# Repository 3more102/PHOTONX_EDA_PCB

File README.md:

# PHOTONX EDA PCB

**Evidence-driven PCB manufacturing-data reconstruction and reverse engineering.**

PHOTONX converts PCB manufacturing evidence into an auditable engineering model: geometry, drills and slots, physical connectivity, reconstructed nets, component and semantic hypotheses, validation evidence, review artifacts, and experimental KiCad output.

> **Core rule: unknown stays unknown.**  
> PHOTONX records provenance, confidence, assumptions, conflicts, omissions, and unresolved state instead of silently turning missing design intent into plausible-looking facts.

**Jump to:** [Quick start](#quick-start) · [Use cases](#where-photonx-fits) · [Flow charts](#reconstruction-flow-chart) · [Pipeline](#reconstruction-pipeline) · [Architecture](#architecture-layers) · [Evidence model](#evidence-model) · [Capabilities](#capability-matrix) · [Python API](#python-api) · [Review checklist](#how-to-review-a-reconstruction) · [Verification](#verification-and-ci) · [Roadmap](#roadmap) · [Documentation](#documentation)

### Visual maps

| Map | Purpose |
|---|---|
| [Reconstruction flow](#reconstruction-flow-chart) | End-to-end manufacturing-data reconstruction |
| [Architecture map](#architecture-layers) | Software and evidence-layer organization |
| [Evidence escalation](#evidence-model) | Observed → derived → inferred → corroborated claims |
| [Human review flow](#how-to-review-a-reconstruction) | Decision path for ambiguous findings |
| [Validation / release flow](#validation-stack) | Tests, round-trip checks, and readiness gates |
| [Parser decision flow](#parsing-and-manufacturing-geometry) | Strict vs permissive handling of unsupported syntax |
| [KiCad export flow](#kicad-export-policy) | Conservative export and native-validation decision path |
| [CLI execution flow](#quick-start) | Command dispatch, bundle generation, optional KiCad export, and exit codes |

---

## Why PHOTONX

PCB manufacturing data preserves **physical implementation** much more reliably than it preserves **original design intent**. A Gerber or drill package can prove that copper, holes, pads, and mechanical features existed; it usually cannot prove the original schematic hierarchy, semantic net names, component values, firmware behavior, or engineering rationale.

PHOTONX is built around that distinction.

| Principle | PHOTONX behavior |
|---|---|
| **Evidence before inference** | Source facts and deterministic derivations are kept separate from hypotheses. |
| **Strict parsing** | Unsupported syntax is rejected or diagnosed rather than silently approximated. |
| **Deterministic reconstruction** | Stable ordering and deterministic IDs make repeated runs auditable and diffable. |
| **Conservative semantics** | Physical copper groups are not automatically promoted to original logical nets. |
| **Explicit uncertainty** | Unknown plating, identity, layer span, values, and intent remain unknown until evidence supports them. |
| **Reproducible validation** | Reconstruction, validation, regression evidence, round-trip checks, and release-readiness logic are kept testable. |

### Current verified snapshot

| Item | Verified state |
|---|---|
| Package | **0.2.0** |
| Python | **3.11+** |
| Main dependencies | **NetworkX**, **Shapely** |
| Verified change set | **PR #54 head `c1fd9fc`, merged as `8ba238d` — 19 Sep 2026** |
| CI matrix | Python **3.11**, **3.12**, **3.13** |
| Test result | **855 passed, 2 warnings** on each CI matrix job |
| CI run | [GitHub Actions run 35431302455](https://github.com/3more102/PHOTONX_EDA_PCB/actions/runs/35431302455) |

PHOTONX is an active engineering platform. It is **not** a complete CAM replacement, electrical sign-off tool, safety certification system, or fabrication guarantee.

---

## Where PHOTONX fits

PHOTONX is most useful when the available evidence is **manufacturing-centric** and the goal is to recover an auditable engineering model without overstating certainty.

| Workflow | What PHOTONX contributes | Boundary |
|---|---|---|
| **Legacy PCB analysis** | Reconstructs geometry, physical connectivity, board features, and evidence-backed hypotheses | Does not recreate unavailable original intent by assumption |
| **Repair / obsolescence investigation** | Helps expose physical nets, component neighborhoods, interfaces, power evidence, and candidate functions | Exact identity still requires markings, BOM, measurements, or other evidence |
| **Design recovery / migration** | Produces structured board data, review artifacts, and experimental KiCad representations | Generated CAD must be reviewed before production use |
| **Manufacturing-data QA** | Surfaces parser diagnostics, geometry issues, validation findings, omissions, and source provenance | Not a fabrication-house sign-off |
| **Research and benchmarking** | Supports deterministic replay, regression fixtures, ground-truth governance, and explicit confidence | Synthetic fixtures remain synthetic evidence |
| **EDA experimentation** | Provides modular parsers, geometry/connectivity APIs, inference layers, exports, and review infrastructure | Production support is limited to declared syntax and semantics |

### PHOTONX is deliberately not

- an automatic “Gerber to perfect schematic” converter;
- a substitute for original source CAD when that source still exists;
- a guarantee that a guessed component, net role, or functional block is correct;
- an SI/PI, EMC, safety, regulatory, or fabrication-certification authority;
- a reason to discard uncertainty that the source package cannot resolve.

---

## Quick start

### Install

```bash
python -m pip install -e ".[test]"
```

### Optional C++17 spatial acceleration

PHOTONX can accelerate spatial broad-phase candidate generation with an optional C++17 shared library while keeping exact Python/Shapely and Euclidean predicates authoritative for connectivity, DRC, and radius acceptance.

```bash
cmake -S native -B build/native -DCMAKE_BUILD_TYPE=Release
cmake --build build/native --config Release
export PHOTONX_NATIVE_LIBRARY="$PWD/build/native/lib/libphotonx_native.so"
pytest -q
```

For a self-contained platform wheel, install the `build` frontend and opt in during wheel creation:

```bash
python -m pip install build
PHOTONX_BUILD_NATIVE=1 python -m build --wheel
```

A normal wheel/install remains Python-only and does not require a compiler. Native-enabled wheels embed the shared library inside the package, so `backend="auto"` can discover it without `PHOTONX_NATIVE_LIBRARY`. See [Native acceleration](docs/NATIVE_ACCELERATION.md) for Windows syntax, the ABI check, safety contract, and staged roadmap.

### Inspect declared parser capabilities

```bash
photonx capabilities
```

### Reconstruct a manufacturing-data directory

```bash
photonx reconstruct examples/PHOTONX_LED_TEST/input --output build/led
```

### Request experimental KiCad PCB output

```bash
photonx reconstruct examples/PHOTONX_LED_TEST/input \
  --output build/led \
  --kicad
```

### Emit review artifacts

```bash
photonx reconstruct examples/PHOTONX_LED_TEST/input \
  --output build/led \
  --review-artifacts
```

This emits a cohesive `review/` bundle with Markdown, JSON, JUnit, SVG, GraphML, and CSV artifacts.

### Request individual review exports

```bash
photonx reconstruct examples/PHOTONX_LED_TEST/input \
  --output build/led \
  --svg --graphml --csv
```

These flags emit `reconstructed.svg`, `reconstructed.graphml`, and CSV net/component tables independently.

### Use permissive parsing intentionally

Strict behavior is preferred. Permissive mode exists for workflows where unsupported constructs should be preserved as diagnostics instead of immediately stopping reconstruction.

```bash
photonx reconstruct examples/PHOTONX_LED_TEST/input \
  --output build/led \
  --permissive
```

### Launch the model-backed GUI

```bash
photonx gui examples/PHOTONX_LED_TEST/input
```

### Run the full regression suite

```bash
pytest -q
```

### Typical end-to-end CLI workflow

```bash
# 1. Inspect the declared syntax boundary
photonx capabilities

# 2. Run a strict reconstruction
photonx reconstruct path/to/manufacturing_data --output build/board

# 3. Review board.json + validation.json before trusting higher-level hypotheses

# 4. Optionally request an editable KiCad PCB representation
photonx reconstruct path/to/manufacturing_data \
  --output build/board \
  --kicad

# 5. Run regression tests before changing parser/reconstruction behavior
pytest -q
```

The strict path is the default because a reconstruction that stops on unsupported syntax is easier to audit than one that silently loses geometry.

---

## Failure behavior is a feature

PHOTONX is designed to fail visibly when evidence or supported semantics are insufficient.

| Situation | Behavior |
|---|---|
| Unsupported syntax in default strict mode | Reconstruction stops instead of silently discarding the construct |
| Unsupported syntax in `--permissive` mode | The condition is retained as a diagnostic for review |
| Reconstructed model contains validation errors | CLI completes the reconstruction bundle and returns exit code **2** |
| Reconstructed model has no validation errors | CLI returns exit code **0** |
| `--kicad` requested | PHOTONX writes the KiCad board plus `kicad_export_report.json`, `kicad_omissions.json`, `kicad_connectivity_roundtrip.json`, and a separate `kicad_validation.txt` native-validation result |
| `kicad-cli` unavailable | The missing native validator is reported; PHOTONX does not present that as successful native validation |
| Unknown semantic fact | The model keeps it unresolved rather than fabricating a convenient value |

This behavior is intentional: a visible limitation is safer and more auditable than a plausible but unsupported reconstruction.

---

## Python API

The package also exposes a small programmatic surface for reconstruction, validation, and export.

```python
from photonx_eda_pcb import (
    ReconstructionConfig,
    reconstruct,
    export_json,
)

config = ReconstructionConfig(
    strict_parsing=True,
    connectivity_tolerance_mm=0.03,
    drill_attach_tolerance_mm=0.15,
)

result = reconstruct("examples/PHOTONX_LED_TEST/input", config)

print(result.validation)
print(len(result.board.nets))

export_json(result.board, "build/led/reconstructed.json")
```

The public package surface currently includes `ReconstructionConfig`, `ReconstructionResult`, `reconstruct`, `load_project`, `validate_board`, `export_json`, `export_kicad`, and `validate_with_kicad_cli`.

---

## What PHOTONX produces

A standard CLI reconstruction writes an auditable reconstruction bundle.

```text
build/led/
├── board.json             # reconstructed BoardModel
├── validation.json        # validation state, issues, and summary
├── reconstructed.json     # explicit JSON export of the BoardModel
├── reconstructed.svg      # only when --svg is requested
├── reconstructed.graphml  # only when --graphml is requested
├── csv/                    # only when --csv is requested
│   ├── nets.csv
│   └── components.csv
├── review/                 # only when --review-artifacts is requested
│   ├── report.md
│   ├── summary.json
│   ├── checks.junit.xml
│   ├── board.svg
│   ├── connectivity.graphml
│   └── csv/
│       ├── nets.csv
│       └── components.csv
└── reconstructed.kicad_pcb  # only when --kicad is requested
```

The repository also contains library-level exporters and reporting infrastructure for additional machine-readable or review-oriented formats, including **SVG, CSV, GraphML, source manifests, JSON reports, Markdown reports, JUnit-style reporting, and KiCad-related artifacts**.

The main review-oriented SVG, GraphML, CSV, Markdown, JSON, and JUnit outputs are exposed through `--review-artifacts` and the granular `--svg`, `--graphml`, and `--csv` switches. Specialized/source-manifest reporting remains available through library APIs.

### Output semantics

| Output | Meaning |
|---|---|
| `board.json` | Canonical reconstructed board data used by the project bundle. |
| `validation.json` | Independent validation status, issues, and reconstruction summary. |
| `reconstructed.json` | Explicit serialized BoardModel export. |
| `reconstructed.kicad_pcb` | Experimental editable KiCad PCB representation when requested. |
| Evidence / review artifacts | Provenance, confidence, diagnostics, review, regression, or release-readiness information depending on the workflow. |

If `kicad-cli` is unavailable, PHOTONX records that state. It does not claim native KiCad validation occurred.

---

## Reconstruction flow chart

**Flow summary:** manufacturing evidence is parsed into normalized physical objects, converted into connectivity and physical-net evidence, enriched with bounded hypotheses, independently validated, then exported and audited. Unknown facts remain explicit instead of being silently invented.

---

## Reconstruction pipeline

The rendered flow chart above shows the complete end-to-end path. The key implementation constraints behind that flow are:

### Architectural invariants

- Spatial indexing narrows candidate pairs; **exact Shapely/Euclidean predicates remain authoritative**.
- A physical copper island is a **physical net**, not automatically the original schematic net.
- Drill or slot plating is not assumed when source evidence does not prove it.
- Unsupported parser constructs are not silently discarded in strict mode.
- Component identity, semantic net roles, schematic hierarchy, and engineering intent remain hypotheses unless evidence supports stronger claims.
- Export omissions and unsupported semantics are surfaced rather than hidden.

---

## Architecture layers

PHOTONX is organized so that lower-confidence interpretation cannot silently rewrite higher-confidence source evidence.

| Layer | Responsibility | Typical outputs |
|---|---|---|
| **1. Discovery** | Identify manufacturing files and infer known/unknown roles | classified source files, unknown-layer diagnostics |
| **2. Parsing** | Convert declared Gerber/Excellon subsets into normalized objects | tracks, pads, drills, slots, routes, outline segments |
| **3. Provenance** | Preserve where reconstructed facts came from | source path, source line/raw evidence, inference evidence |
| **4. Geometry** | Represent physical objects in normalized units | deterministic physical geometry |
| **5. Connectivity** | Build contact relationships from copper geometry | physical graph and connected islands |
| **6. Physical nets** | Assign deterministic groups to connected copper | `NetGroup` objects and object back-references |
| **7. Inference** | Build bounded hypotheses from physical/evidence context | component, role, protocol, and functional candidates |
| **8. Validation** | Check model invariants independently of reconstruction | errors, warnings, validation status |
| **9. Export / review** | Emit machine-readable and human-review artifacts | JSON, reports, GUI views, experimental KiCad data |
| **10. Regression / readiness** | Check repeatability, compatibility, round-trip, and release evidence | CI results, baselines, readiness findings |

### Canonical core model

The top-level reconstruction path centers on a `BoardModel` containing these core object families:

| Model object | Role |
|---|---|
| `Track` | Copper line segment with width, layer, provenance, and optional physical-net back-reference |
| `PadCandidate` | Reconstructed pad-like copper feature |
| `DrillHit` | Drill evidence with diameter, tool information, provenance, and plating state |
| `SlotFeature` | Reconstructed mechanical/plated-slot evidence |
| `RoutedPath` | Supported Excellon routed-path geometry |
| `OutlineSegment` | Board-outline geometry |
| `NetGroup` | Deterministic physical connectivity group with confidence and provenance |
| `ComponentHypothesis` | Evidence-backed component grouping with confidence and explicit evidence |
| `ParseDiagnostic` | Structured parser warning/error information |

The model is intentionally narrower than the full set of higher-level analysis packages: domain inference is layered on top of physical evidence rather than embedded into raw parser objects.

---

## Evidence model

Every important reconstructed statement should fall into one of four states:

| State | Meaning | Example |
|---|---|---|
| **Observed** | Present directly in a source artifact | Gerber flash geometry, Excellon drill coordinate, source attribute |
| **Derived** | Deterministically computed from observed evidence | Copper contact, board bounds, physical connected component |
| **Inferred** | Hypothesis supported by evidence and confidence | Component type, semantic net role, functional block |
| **Unknown** | Not defensibly recoverable from available evidence | Missing value/MPN, original intent, unproven plating or layer span |

This distinction feeds provenance, conflict handling, review workflows, validation, exports, and readiness logic.

### Examples of conservative interpretation

- Connected copper does **not** prove an original logical net name.
- A pad pattern match does **not** prove a BOM identity.
- A likely clock or reset is a **candidate**, not proof of firmware behavior.
- A generated schematic page is a **review view**, not proof of the original hierarchy.
- A generated net class is a reconstructed engineering recommendation, not necessarily the original design rule.
- A readiness pass is a software/evidence milestone, not electrical or fabrication certification.

---

## Capability matrix

**Status legend:** **Implemented** = supported by the current production path; **Partial** = supported only for a declared subset; **Experimental** = usable but not presented as complete production equivalence; **Not inferable** = source data generally cannot prove it; **Not implemented** = intentionally unsupported in the production path.

### Parsing and manufacturing geometry

| Capability | Status | Current behavior |
|---|---|---|
| Gerber linear draws / flashes | **Partial** | C/R/O flashes plus standard P regular-polygon D03 flashes are supported. C/R/O/P D03 flashes may include the standard centered round-hole modifier and are materialized with transparent-hole semantics when needed. Circular D01 draws remain centerline tracks; rectangular D01 sweeps are exact CopperRegion polygons and obround D01 sweeps use deterministic 0.005 mm chord-error-bounded polygonization. Arbitrary finite LR is supported for R/O sweeps/flashes and P flashes/draws; solid P D01 sweeps are exact CopperRegion convex sweeps, while holed P D01 and other holed D01/G02/G03 draws remain fail-closed |
| Gerber unit declaration | **Required** | `MO` or supported legacy `G70/G71` must establish units before dimensional data; conflicting unit switches fail closed |
| Gerber X2 file polarity | **Partial** | Explicit `Positive` is accepted; `Negative` fails closed because absence-of-material image inversion is not yet modeled |
| Gerber layer polarity | **Partial** | `LPD` is supported; `LPC` composes supported G36/G37 regions, C/R/O/P D03 flashes (including supported round-hole variants), linear C/R/O/P D01 aperture sweeps, and circular-aperture G02/G03 tracks in source order. Aperture holes are transparent within the flash operation rather than separate clear operations. P outer boundaries are exact polygons; C/O curved boundaries use deterministic inscribed chords with a 0.005 mm maximum chord-error target. Tessellated circular-aperture arc tracks retain a conservative <=0.010 mm combined boundary-error budget; outline geometry remains fail-closed |
| Gerber aperture transforms | **Partial** | Modal LM/LR/LS applies to the original aperture at object creation. Circles accept arbitrary LR; R/O linear D01 sweeps and D03 flashes accept arbitrary finite LR. Orthogonal R/O flashes stay PadCandidate objects; non-orthogonal flashes are materialized as CopperRegion polygons with exact rectangular or bounded obround geometry |
| Gerber C/R/O/P apertures | **Implemented subset** | Positive-size C/R/O plus standard regular-polygon P apertures (3–12 vertices) are modeled for D03. P template rotation, LM-before-LR, LS, IR, step-repeat, LPC and optional centered round holes are supported. Solid P D01 linear sweeps are exact; holed P D01 remains fail-closed. The specification-defined zero-diameter C aperture is accepted as a legal no-image object. Other holed D01/G02/G03 draws remain fail-closed |
| Gerber step-and-repeat | **Implemented subset** | Supported geometry expands deterministically; malformed/non-positive/over-limit SR state fails closed and suppresses permissive file geometry |
| Gerber circular arcs | **Partial** | G75 multi-quadrant arcs use signed I/J offsets; bounded legacy G74 single-quadrant arcs resolve unsigned I/J distances only when one <=90° center candidate is unambiguous; deterministic tessellation with explicit provenance |
| Gerber simple aperture macros | **Partial** | Origin-centered circles, exact centered Code-20/Code-2 vector-line, Code-21 center-line, deprecated Code-22 lower-left rectangles, reducible Code-4 rectangles/regular polygons, and origin-centered Code-5 regular polygons use exact C/R/P paths. Ordered `$n=expression` macro variables are evaluated from AD parameters; undefined variables are zero and redefinition is invalid. Code-1 circle reduction requires exactly four or five finite modifiers and finite unit conversion. Other valid single-positive Code-4 simple contours with 3–5000 vertices—including irregular, concave, and off-center shapes—are emitted exactly as CopperRegion D03 flashes on material layers. Invalid/self-touching outlines, general Code-4 D01 sweeps, and Edge.Cuts flashes remain fail-closed |
| Gerber regions / complex macros | **Partial** | G36/G37 statements support multiple closed linear/G74/G75 contours plus bounded cut-in holes; LPD/LPC streams containing supported regions, C/R/O/P D03 flashes, valid general Code-4 outline-macro D03 flashes, and supported linear D01 geometry are composed in order and materialized as explicit CopperRegion shells/holes with provenance. C/O flash and track-cap polygonization is explicitly evidenced and bounded to 0.005 mm chord error. Disjoint/mixed-axis/invalid cut-ins, LPC with outlines, Edge.Cuts regions, aperture blocks, and complex macros remain fail-closed |
| Excellon point drill hits | **Implemented** | Drill hits with explicit metric/inch units and positive tool diameters; undeclared-unit and zero-diameter tools fail closed |
| Excellon coordinate mode | **Implemented** | Absolute `G90` / `ICI,OFF` and incremental `G91` / `ICI,ON` coordinates are supported for drill hits, G85 slots, and routed endpoints |
| Excellon G85 straight slots | **Implemented** | Straight canned slots are reconstructed in absolute and incremental modes; malformed slot syntax still fails closed with permissive geometry suppression |
| Excellon linear routing | **Implemented** | G00/M15/G01/M16 routes supported; malformed commands and invalid route-state transitions fail closed |
| Excellon routed arcs | **Partial** | Bounded I/J and standard XNC X/Y/A radius arcs (<=180°) are supported; invalid/unsupported arcs fail closed and suppress permissive file geometry |
| Strict / permissive parser modes | **Implemented** | Strict fails on unsupported syntax; permissive records diagnostics |
| Parser conformance harness | **Implemented** | Executable support-boundary regression coverage |

### Physical reconstruction

PHOTONX contains infrastructure for:

- shared geometry representation for tracks and reconstructed pads;
- deterministic coordinate and tolerance handling;
- board-material reconstruction from outlines and cutouts;
- spatial candidate indexing;
- same-layer copper connectivity plus evidence-gated cross-layer edges through proven plated via spans;
- drill-to-pad association;
- via-span evidence that preserves the exact supporting pad identities and fails closed when plating is unknown;
- copper-zone contact analysis;
- annular-ring checks;
- drill-to-copper clearance;
- board-edge and cutout-aware clearance;
- mechanical hole/slot geometry and clearance;
- deterministic physical-net grouping.

### Semantic and component reconstruction

PHOTONX contains evidence and inference layers for:

- component and footprint hypotheses;
- reference-designator recovery;
- component values, footprints, MPN candidates, and identity evidence;
- BOM and pick-and-place reconciliation;
- board variants and DNP handling;
- net-name evidence;
- signal roles and bus grouping;
- clock and reset candidates;
- differential-pair candidates;
- I2C, SPI, UART, and CAN evidence;
- connector pin-function hypotheses;
- MCU / SoC peripheral mapping;
- FPGA bank evidence;
- SWD / JTAG debug-interface candidates;
- DDR-style topology candidates;
- repeated circuits and functional blocks;
- analog, power, protection, termination, bias, and conditioning hypotheses.

These are **evidence-backed hypotheses**. They are not automatically the original design intent.

### Schematic reconstruction and editing

The repository includes infrastructure for:

- schematic graph generation;
- functional-block clustering;
- generated schematic pages;
- editable schematic state;
- staged edits and human-review routing;
- deterministic auto-layout;
- page partitioning and wire routing;
- undo/redo and command-bus integration;
- confidence/provenance-aware editing;
- structured KiCad schematic export;
- deterministic export snapshots;
- schematic round-trip checks.

Generated hierarchy and layout remain review-oriented reconstructions.

### Engineering analysis

Analysis layers include areas such as:

- DRC and ERC;
- copper width and clearance;
- annular ring and mechanical clearance;
- edge/cutout clearance;
- return-path evidence;
- power-tree and supply-domain reconstruction;
- decoupling quality;
- current-capacity evidence;
- thermal-risk prioritization;
- signal-integrity risk;
- fabrication-yield risk;
- assembly manufacturability;
- test-point and testability analysis;
- length groups;
- generated candidate constraints and net classes.

Risk scores and synthesized constraints are review aids. They do **not** replace dedicated SI/PI, thermal, safety, EMC, regulatory, or manufacturer DFM tools.

---

## KiCad export policy

KiCad export is intentionally conservative.

- Pads, tracks, nets, and board outlines can be represented in the experimental PCB export path.
- NPTH slots can be exported when their semantics are known.
- A plated slot requires evidence sufficient to infer a padstack.
- A slot with unknown plating is skipped rather than guessed.
- Arbitrary Excellon routed paths are explicitly omitted where equivalent KiCad semantics are not implemented.
- Native KiCad validity is only claimed when `kicad-cli` actually runs.

This policy is designed to make omissions visible instead of producing silently misleading CAD.

---

## Included end-to-end regression fixture

`examples/PHOTONX_LED_TEST/` is intentionally **synthetic**. It is a compact regression fixture, not a claimed recovery of an unknown production PCB.

Expected model:

| Object | Expected count |
|---|---:|
| Pad candidates | 6 |
| Copper tracks | 4 |
| Drill hits | 6 |
| Board-outline segments | 4 |
| Physical copper islands | 3 |

The fixture exercises Gerber flashes and linear copper draws, Excellon point drills, drill-to-pad evidence association, physical connectivity, component hypotheses, validation, JSON output, and KiCad export.

Synthetic fixtures elsewhere in the repository are likewise test evidence, not recovered production boards. External/reference datasets should carry source, license, checksum, and admission metadata before being treated as ground truth.

---

## Evidence, provenance, review, and release governance

The repository contains infrastructure for:

- source and line provenance;
- evidence records and confidence;
- semantic conflicts;
- unresolved-state tracking;
- review queues and checkpoints;
- annotations;
- source-change tracking;
- deterministic replay;
- invalidation auditing;
- fault injection;
- regression baselines;
- ground-truth matrices;
- benchmark governance;
- release manifests;
- change control and ECO tracking;
- compatibility freeze checks;
- release-candidate assembly;
- manufacturing-package audit;
- production-board validation;
- Development / Research / Review / Manufacturing-export-candidate release profiles;
- milestone-readiness aggregation.

### Phase-70 readiness

The Phase-70 layer aggregates release, manufacturing, change-control, compatibility, replay, benchmark, semantic, traceability, and round-trip evidence.

A Phase-70 pass is an **internal software/evidence milestone only**. It is not a safety certificate, electrical sign-off, regulatory approval, fabrication approval, or proof that unknown original design intent has been recovered.

See [docs/PHASE70_READINESS.md](docs/PHASE70_READINESS.md).

---

## How to review a reconstruction

A PHOTONX result should be reviewed from the **lowest-level evidence upward**. Do not start by trusting the most semantic output.

1. **Check parser diagnostics.** Confirm that no important source constructs were rejected, skipped, or only accepted permissively.
2. **Check the outline and geometry.** Confirm board bounds, copper objects, drills, slots, and routed geometry against the source package.
3. **Check physical connectivity.** Review copper islands and drill/via associations before accepting any semantic net interpretation.
4. **Check unresolved evidence.** Unknown plating, layer spans, component identity, values, and semantic roles should remain visible.
5. **Check validation errors and warnings.** A warning is not automatically harmless; it means the reviewer must decide whether it matters for the intended use.
6. **Check inference confidence and evidence.** Treat component, protocol, functional-block, and schematic hypotheses according to their supporting evidence.
7. **Check export omissions.** Confirm what the chosen exporter could not represent.
8. **Check native-tool validation where relevant.** For KiCad, distinguish PHOTONX structural export from an actual `kicad-cli` validation run.
9. **Check regression/readiness evidence.** A green CI run proves the asserted software tests passed; it does not certify the reconstructed board electrically.

### Evidence escalation rule

```text
Source artifact
    ↓
Observed fact
    ↓ deterministic transformation
Derived physical fact
    ↓ bounded reasoning + evidence
Inference / hypothesis
    ↓ independent corroboration
Higher-confidence engineering claim
```

At no point should a missing source fact move upward merely because a plausible answer exists.

---

## Validation stack

PHOTONX separates different kinds of confidence instead of collapsing them into one “pass/fail” claim.

| Layer | Question answered |
|---|---|
| **Parser validation** | Did PHOTONX understand the source syntax it claims to support? |
| **Model validation** | Is the reconstructed internal model structurally consistent? |
| **Engineering checks** | Are there geometry, clearance, connectivity, DRC/ERC, or evidence issues to review? |
| **Regression tests** | Did a code change preserve previously asserted behavior? |
| **Round-trip checks** | Did an export/import path preserve the semantics that path claims to support? |
| **Readiness gates** | Is the software/evidence package internally ready for the declared profile or milestone? |

A pass at one layer does not imply a pass at the others.

---

## Verification and CI

The GitHub Actions matrix runs the regression suite on:

- Python 3.11
- Python 3.12
- Python 3.13

For the change set merged as **`8ba238d`** (verified on PR #54 head **`c1fd9fc`**), each matrix job completed successfully with:

```text
855 passed, 2 warnings
```

The two pytest warnings are collection warnings for a model class named `TestPointCandidate`; the CI jobs still complete successfully.

[Open the verified workflow run](https://github.com/3more102/PHOTONX_EDA_PCB/actions/runs/35431302455).

---

## Trust boundaries and known limitations

PHOTONX intentionally refuses to convert absence of evidence into certainty.

### What PHOTONX can establish or reconstruct

Depending on the source package and supported syntax, PHOTONX can establish or derive physical geometry, drills and supported slots/routes, copper contact, physical connected components, board features, evidence associations, validation issues, and bounded hypotheses.

### What PHOTONX cannot automatically know

Without independent evidence, manufacturing geometry generally cannot prove:

- original semantic net names;
- original schematic hierarchy;
- exact component values or MPNs;
- firmware configuration or behavior;
- dielectric/material stack-up properties;
- original design rules;
- electrical function or engineering rationale;
- plating or layer span where source evidence is absent;
- safety, EMC, regulatory, or fabrication approval.

### Important parser limitations

- The production Gerber path is still a declared subset, not the full language.
- Gerber dimensional data requires an explicit `MO` declaration or supported legacy `G70/G71`; permissive parsing suppresses the file when units are missing or later conflict instead of assuming millimeters or mixing unit systems.
- Legacy Gerber incremental coordinates are supported through `G91` and FS `I` notation such as `%FSLIX...*%`: X/Y values accumulate from the preceding coordinate position, `G90`/FS `A` restore absolute notation, and arc I/J values remain center offsets from the arc start.
- X2 `.FilePolarity,Negative` is not treated as ordinary metadata: strict parsing rejects it, while permissive parsing suppresses geometry to avoid interpreting clearance as material.
- Gerber `%LPC*%` clear layer polarity uses ordered polygon composition for supported G36/G37 regions, C/R/O/P D03 flashes, linear C/R/O/P D01 aperture sweeps, and circular-aperture G02/G03 tracks. Regions, R flashes, and R linear sweeps are exact; C/O curved boundaries use deterministic inscribed-chord polygonization with explicit `gerber_flash_polygonization` / `gerber_track_polygonization` evidence and a 0.005 mm maximum chord-error target. Tessellated circular-aperture arc tracks retain the documented combined error bound; outlines remain fail-closed.
- Modern `LM/LR/LS` aperture transforms are modal and apply to the original aperture at object creation. PHOTONX supports LM for centered symmetric C/R/O geometry, positive LS scaling, arbitrary LR for circles, and arbitrary finite LR for rectangle/obround linear sweeps and flashes. Orthogonal R/O flashes remain PadCandidate objects; non-orthogonal flashes are materialized as CopperRegion polygons with exact rectangular or explicitly bounded obround geometry.
- Deprecated positive whole-image polarity `%IPPOS*%` plus `MI`, `SF`, `OF`, and orthogonal `IR` image transforms are modeled within the declared subset; `%IPNEG*%` remains fail-closed because whole-image inversion is not modeled. Legacy IP/AS/IN/MI/SF/OF/IR header state must appear before the first coordinate statement (including D02 moves), and duplicate/late header diagnostics are strict preflight blockers. SF scales coordinate data only: apertures and step-repeat distances remain unchanged; uniform SF supports circular arcs while anisotropic SF arcs fail closed rather than becoming implicit ellipses. Both `ASAXBY` and `ASAYBX` are accepted as output-device-only no-ops. Legacy `IN/LN` names are retained as diagnostics, `G55/M01` are harmless no-ops, and `M00` terminates parsing like `M02`.
- Gerber step-and-repeat is fail-closed when the SR statement is malformed, has non-positive repeat counts, or exceeds the configured expansion limit; permissive parsing suppresses the file rather than flattening a panel to one instance.
- G75 multi-quadrant circular arcs are supported only for I/J center offsets with circular draw apertures and are represented by explicitly evidenced tessellation.
- Single positive origin-centered circle macros, exact centered Code-20 vector-line (including deprecated Code-2 alias), Code-21 center-line, deprecated Code-22 lower-left rectangles, and origin-centered Code-5 regular polygons are supported as exact C/R/P apertures. Finite rectangle primitive rotations are preserved exactly and centered Code-20 segments may be arbitrarily oriented; Code-5 polygons require an integer 3–12 vertex count, positive circumscribed diameter, and finite rotation. Supported macro geometry composes with LM/LR/LS and whole-image IR; non-centered, subtractive, multi-primitive, and other complex macro geometry remains fail-closed. Legacy G74 single-quadrant arcs are supported only for unsigned I/J distances when one center candidate is unambiguous and the sweep is at most 90°. Multi-contour regions with linear/G74/G75 circular boundaries are supported; each contour must be explicitly closed. Files containing supported regions, solid C/R/O D03 flashes, and linear circular-aperture D01 tracks may switch between LPD and LPC: operations are composed in source order, so clear geometry subtracts only material accumulated before it and later dark geometry may refill cleared areas. Multiple cut-ins in one contour are reconstructed as explicit holes when every bridge is a fully-coincident opposite horizontal/vertical linear pair and all cut-ins in that contour share the same direction. Disjoint fully-coincident cut-in topology, mixed-axis/invalid cut-ins, LPC mixed with tessellated arc tracks or outlines, Edge.Cuts regions, and aperture blocks remain fail-closed.
- Legacy Excellon `G91` / `ICI,ON` incremental coordinates are supported for drill hits, G85 canned slots, and routed endpoints. G85 starts accumulate from the preceding coordinate and G85 ends accumulate from the slot start; routed-arc I/J values remain center offsets.
- Excellon tool diameters require explicit units before their definition; permissive parsing suppresses the file after an undeclared-unit violation rather than guessing millimeters.
- Excellon tool diameters must also be positive; zero-diameter tools are rejected in strict mode and suppress permissive file geometry instead of creating zero-width physical features.
- Excellon G02/G03 routed arcs are supported for the bounded I/J center-offset subset and standard XNC X/Y/A radius form with <=180° sweep; invalid geometry or unsupported arc dialects fail closed, and permissive parsing suppresses file geometry rather than outputting a route with the failed arc omitted.
- Excellon route/slot state violations are also fail-closed: malformed G00/G01 or G85 syntax, tool/drill/mode changes while routing, empty route termination, and unterminated routes suppress permissive file geometry instead of producing a partial board.
- Some low-level helpers may recognize constructs that the high-level reconstruction path does not yet claim as production support.

Before treating output as production evidence, review the current parser capabilities and the relevant domain documentation.

---

## Repository map

```text
src/photonx_eda_pcb/
├── parsers/                     # Gerber / Excellon parsing and diagnostics
├── geometry/                    # Geometry helpers
├── geometry_kernel/             # Shared exact geometry representation
├── spatial/                     # Spatial utilities
├── spatial_connectivity/        # Candidate indexing
├── connectivity/                # Copper graph / drill association / physical nets
├── stackup/                     # Stack-up evidence
├── via_span/                    # Via-span candidates and validation
├── zones/                       # Copper-zone analysis
├── footprints/                  # Footprint inference
├── inference/                   # Component hypotheses
├── component_identity/          # Identity resolution
├── net_naming/                  # Semantic net evidence
├── schematic_graph/             # Reconstructed schematic topology
├── functional_blocks/           # Functional clustering
├── schematic_editor/            # Editable schematic model
├── schematic_autolayout/        # Deterministic layout
├── kicad_schematic_export/      # Structured schematic export
├── drc/                         # Design-rule checks
├── erc/                         # Electrical-rule checks
├── evidence_database/           # Evidence storage
├── review_workflow/             # Human-review routing
├── regression_corpus/           # Regression datasets / expectations
├── production_board_validation/ # Production-readiness checks
├── production_release_profiles/ # Release profiles
├── release_candidate/           # Release assembly
├── milestone_readiness/         # Phase-70 readiness
├── exporters/                   # JSON / KiCad / SVG / CSV / GraphML and related exports
├── reporting/                   # Structured reporting
├── pipeline_stages/             # Reconstruction stage orchestration
├── pipeline_dag/                # Dependency and impact model
├── gui/                         # Tkinter viewer
└── ...
```

The repository contains additional domain-specific packages; this map is intentionally thematic rather than exhaustive.

---

## Roadmap

The current roadmap keeps the highest-risk gaps explicit rather than masking them behind permissive behavior.

**Primary future work includes:**

- broader Gerber support, including regions, more aperture macro primitives/blocks, and additional legacy/vendor arc dialects;
- richer Gerber X2 attribute handling;
- broader Excellon route/slot dialect support beyond standard XNC, including additional vendor variants;
- broader multilayer via-span reasoning beyond the current pad-evidenced plated-barrel bridge;
- stronger footprint clustering and component evidence;
- more validation against boards with independently known ground truth.

See [docs/ROADMAP.md](docs/ROADMAP.md) and the detailed [Phase 59–70 roadmap](docs/CODING_ROADMAP_PHASE59_70.md).

### What “done” means for a new capability

A feature is not considered mature merely because one example works. The intended path is:

1. declare the supported syntax/semantic boundary;
2. preserve provenance and diagnostics;
3. add focused regression fixtures;
4. validate deterministic behavior;
5. test failure/unsupported cases;
6. document export or inference limitations;
7. only then promote the capability in the README matrix.

---

## Documentation

### Start here

| Topic | Document |
|---|---|
| Architecture | [docs/ARCHITECTURE.md](docs/ARCHITECTURE.md) |
| Evidence model | [docs/EVIDENCE_MODEL.md](docs/EVIDENCE_MODEL.md) |
| Connectivity evidence | [docs/CONNECTIVITY_EVIDENCE.md](docs/CONNECTIVITY_EVIDENCE.md) |
| Copper connectivity solver | [docs/COPPER_CONNECTIVITY_SOLVER.md](docs/COPPER_CONNECTIVITY_SOLVER.md) |
| Multilayer connectivity | [docs/MULTILAYER_CONNECTIVITY.md](docs/MULTILAYER_CONNECTIVITY.md) |
| Parser architecture | [docs/PARSER_ARCHITECTURE.md](docs/PARSER_ARCHITECTURE.md) |
| Parser conformance | [docs/PARSER_CONFORMANCE_SUITE.md](docs/PARSER_CONFORMANCE_SUITE.md) |
| Parser diagnostics | [docs/PARSER_DIAGNOSTICS.md](docs/PARSER_DIAGNOSTICS.md) |
| Production-board validation | [docs/PRODUCTION_BOARD_VALIDATION.md](docs/PRODUCTION_BOARD_VALIDATION.md) |
| Review workflow | [docs/REVIEW_WORKFLOW.md](docs/REVIEW_WORKFLOW.md) |
| KiCad schematic export | [docs/KICAD_SCHEMATIC_EXPORT.md](docs/KICAD_SCHEMATIC_EXPORT.md) |
| KiCad slot round-trip | [docs/KICAD_SLOT_ROUNDTRIP.md](docs/KICAD_SLOT_ROUNDTRIP.md) |
| Release profiles | [docs/PRODUCTION_RELEASE_PROFILES.md](docs/PRODUCTION_RELEASE_PROFILES.md) |
| Phase-70 readiness | [docs/PHASE70_READINESS.md](docs/PHASE70_READINESS.md) |
| Phase 59–70 roadmap | [docs/CODING_ROADMAP_PHASE59_70.md](docs/CODING_ROADMAP_PHASE59_70.md) |
| Project health | [docs/PROJECT_HEALTH.md](docs/PROJECT_HEALTH.md) |

---

## Primary format references

PHOTONX development is intended to remain grounded in authoritative format documentation.

- Ucamco Gerber format/specification and conformance resources  
  https://www.ucamco.com/en/guest/downloads/gerber-format
- Ucamco Gerber reference information  
  https://www.ucamco.com/en/gerber
- KiCad PCB S-expression format  
  https://dev-docs.kicad.org/en/file-formats/sexpr-pcb/
- KiCad S-expression syntax  
  https://dev-docs.kicad.org/en/file-formats/sexpr-intro/index.html

---

## Developer workflow

A safe change to PHOTONX should normally follow this sequence:

```text
Reproduce → Add fixture/test → Implement → Validate provenance →
Run focused tests → Run full pytest → Inspect changed outputs → Push → Verify CI
```

Recommended local loop:

```bash
python -m pip install -e ".[test]"

# focused test while developing
pytest -q tests/path_to_relevant_test.py

# full regression before proposing the change
pytest -q
```

For parser changes, add a regression fixture **before** relaxing behavior. For inference changes, preserve confidence/evidence boundaries. For exporters, do not turn unknown semantics into definite CAD constructs merely to make an output file look complete.

See [docs/TESTING.md](docs/TESTING.md), [docs/QUALITY_GATES.md](docs/QUALITY_GATES.md), and [CONTRIBUTING.md](CONTRIBUTING.md).

---

## Contributing

Contributions should preserve PHOTONX's evidence boundaries: do not silently accept unsupported syntax, invent semantic facts, or replace explicit unknown state with convenience assumptions.

See [CONTRIBUTING.md](CONTRIBUTING.md) for repository contribution guidance.

---

## Engineering philosophy

PHOTONX favors:

- strict parsing over silent acceptance;
- deterministic output over accidental ordering;
- evidence over guesses;
- confidence and provenance over fake certainty;
- exact predicates after spatial candidate filtering;
- parity and regression tests before replacing reference algorithms;
- synthetic fixtures over unverified anecdotes;
- explicit unsupported states over hidden partial behavior;
- compatibility bridges over abrupt API breakage;
- reproducible release evidence over informal “looks good” sign-off.

The goal is not to declare reverse engineering “finished.” The goal is to make every reconstructed claim progressively more **auditable, reproducible, testable, reviewable, and defensible**.

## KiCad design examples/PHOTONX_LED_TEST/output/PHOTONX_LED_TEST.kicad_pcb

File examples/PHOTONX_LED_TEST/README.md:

# PHOTONX_LED_TEST

This directory is a **synthetic regression fixture**, not a claim that PHOTONX recovered an unknown production board.

It exercises Gerber flashes/linear copper draws, Excellon point drills, drill-to-pad evidence association, physical connectivity, component hypotheses, validation, JSON output and KiCad export.

Expected model: 6 pad candidates, 4 copper tracks, 6 drill hits, 4 outline segments and 3 physical copper islands.

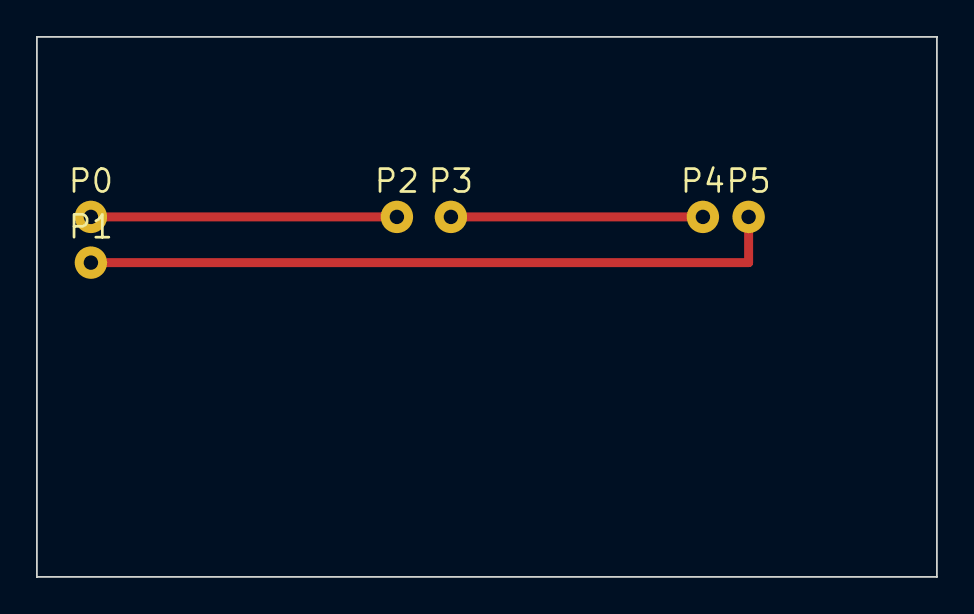
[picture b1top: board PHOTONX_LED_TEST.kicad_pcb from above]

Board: 2 copper layers, 50.0 x 30.0 mm, 6 parts (0 on the bottom side), 3 nets.

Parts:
P0, P1, P2, P3, P4, P5: RecoveredPad

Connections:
N$$1: P0.1, P2.1
N$$2: P1.1, P5.1
N$$3: P3.1, P4.1
